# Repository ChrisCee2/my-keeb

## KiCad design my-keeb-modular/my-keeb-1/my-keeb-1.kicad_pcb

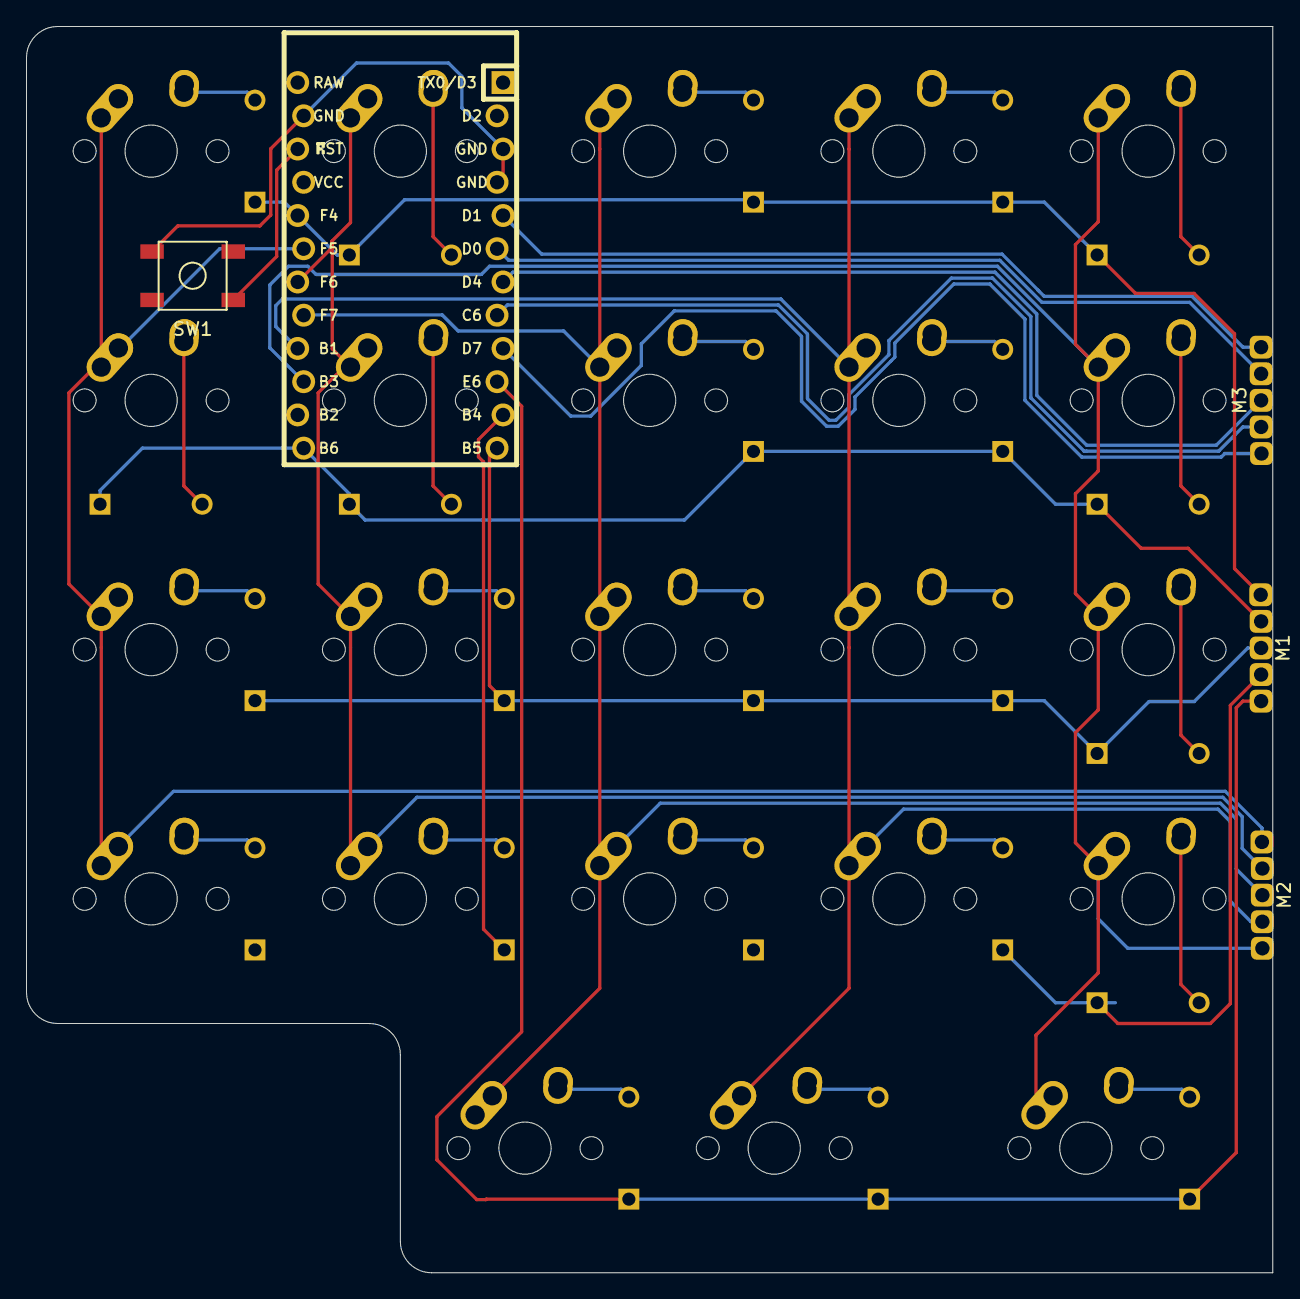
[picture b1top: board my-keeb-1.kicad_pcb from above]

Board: 2 copper layers, 95.2 x 95.2 mm, 51 parts (1 on the bottom side), 40 nets.

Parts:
D1, D2, D3, D4, D5, D6, D7, D8, D9, D10, D11, D12, D13, D14, D15, D16, D17, D18, D19, D20, D21, D22, D23: SOD-123; Diode-Hybrid-Back
M1, M2, M3: 1x5
MX1, MX2, MX3, MX4, MX5, MX6, MX7, MX8, MX9, MX10, MX11, MX12, MX13, MX14, MX15, MX16, MX17, MX18, MX19, MX20, MX21, MX22: MX-NoLED; MX-1U-NoLED
MX23: MX-NoLED; MX-1.5U-NoLED
SW1: SW_Push; SKQG-1155865
U1: ProMicro; ArduinoProMicro-ZigZag

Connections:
COL0: M2.1, MX1.1, MX2.1, MX3.1, MX4.1, U1.19
COL1: M2.2, MX5.1, MX6.1, MX7.1, MX8.1, U1.18
COL2: M2.3, MX9.1, MX10.1, MX11.1, MX12.1, MX13.1, U1.17
COL3: M2.4, MX14.1, MX15.1, MX16.1, MX17.1, MX18.1, U1.16
COL4: M2.5, MX19.1, MX20.1, MX21.1, MX22.1, MX23.1, U1.15
COL5: M3.1, U1.9
COL6: M3.2, U1.8
COL7: M3.3, U1.7
COL8: M3.4, U1.6
COL9: M3.5, U1.5
GND: SW1.2, U1.3, U1.4, U1.23
unnamed: D1.2, MX1.2
unnamed: D2.2, MX2.2
unnamed: D3.2, MX3.2
unnamed: D4.2, MX4.2
unnamed: D5.2, MX5.2
unnamed: D6.2, MX6.2
unnamed: D7.2, MX7.2
unnamed: D8.2, MX8.2
unnamed: D9.2, MX9.2
unnamed: D10.2, MX10.2
unnamed: D11.2, MX11.2
unnamed: D12.2, MX12.2
unnamed: D13.2, MX13.2
unnamed: D14.2, MX14.2
unnamed: D15.2, MX15.2
unnamed: D16.2, MX16.2
unnamed: D17.2, MX17.2
unnamed: D18.2, MX18.2
unnamed: D19.2, MX19.2
unnamed: D20.2, MX20.2
unnamed: D21.2, MX21.2
unnamed: D22.2, MX22.2
unnamed: D23.2, MX23.2
unnamed: SW1.1, U1.22
ROW0: D1.1, D5.1, D9.1, D14.1, D19.1, M1.1, U1.20
ROW1: D2.1, D6.1, D10.1, D15.1, D20.1, M1.2, U1.13
ROW2: D3.1, D7.1, D11.1, D16.1, D21.1, M1.3, U1.12
ROW3: D4.1, D8.1, D12.1, D17.1, D22.1, M1.4, U1.11
ROW4: D13.1, D18.1, D23.1, M1.5, U1.10
